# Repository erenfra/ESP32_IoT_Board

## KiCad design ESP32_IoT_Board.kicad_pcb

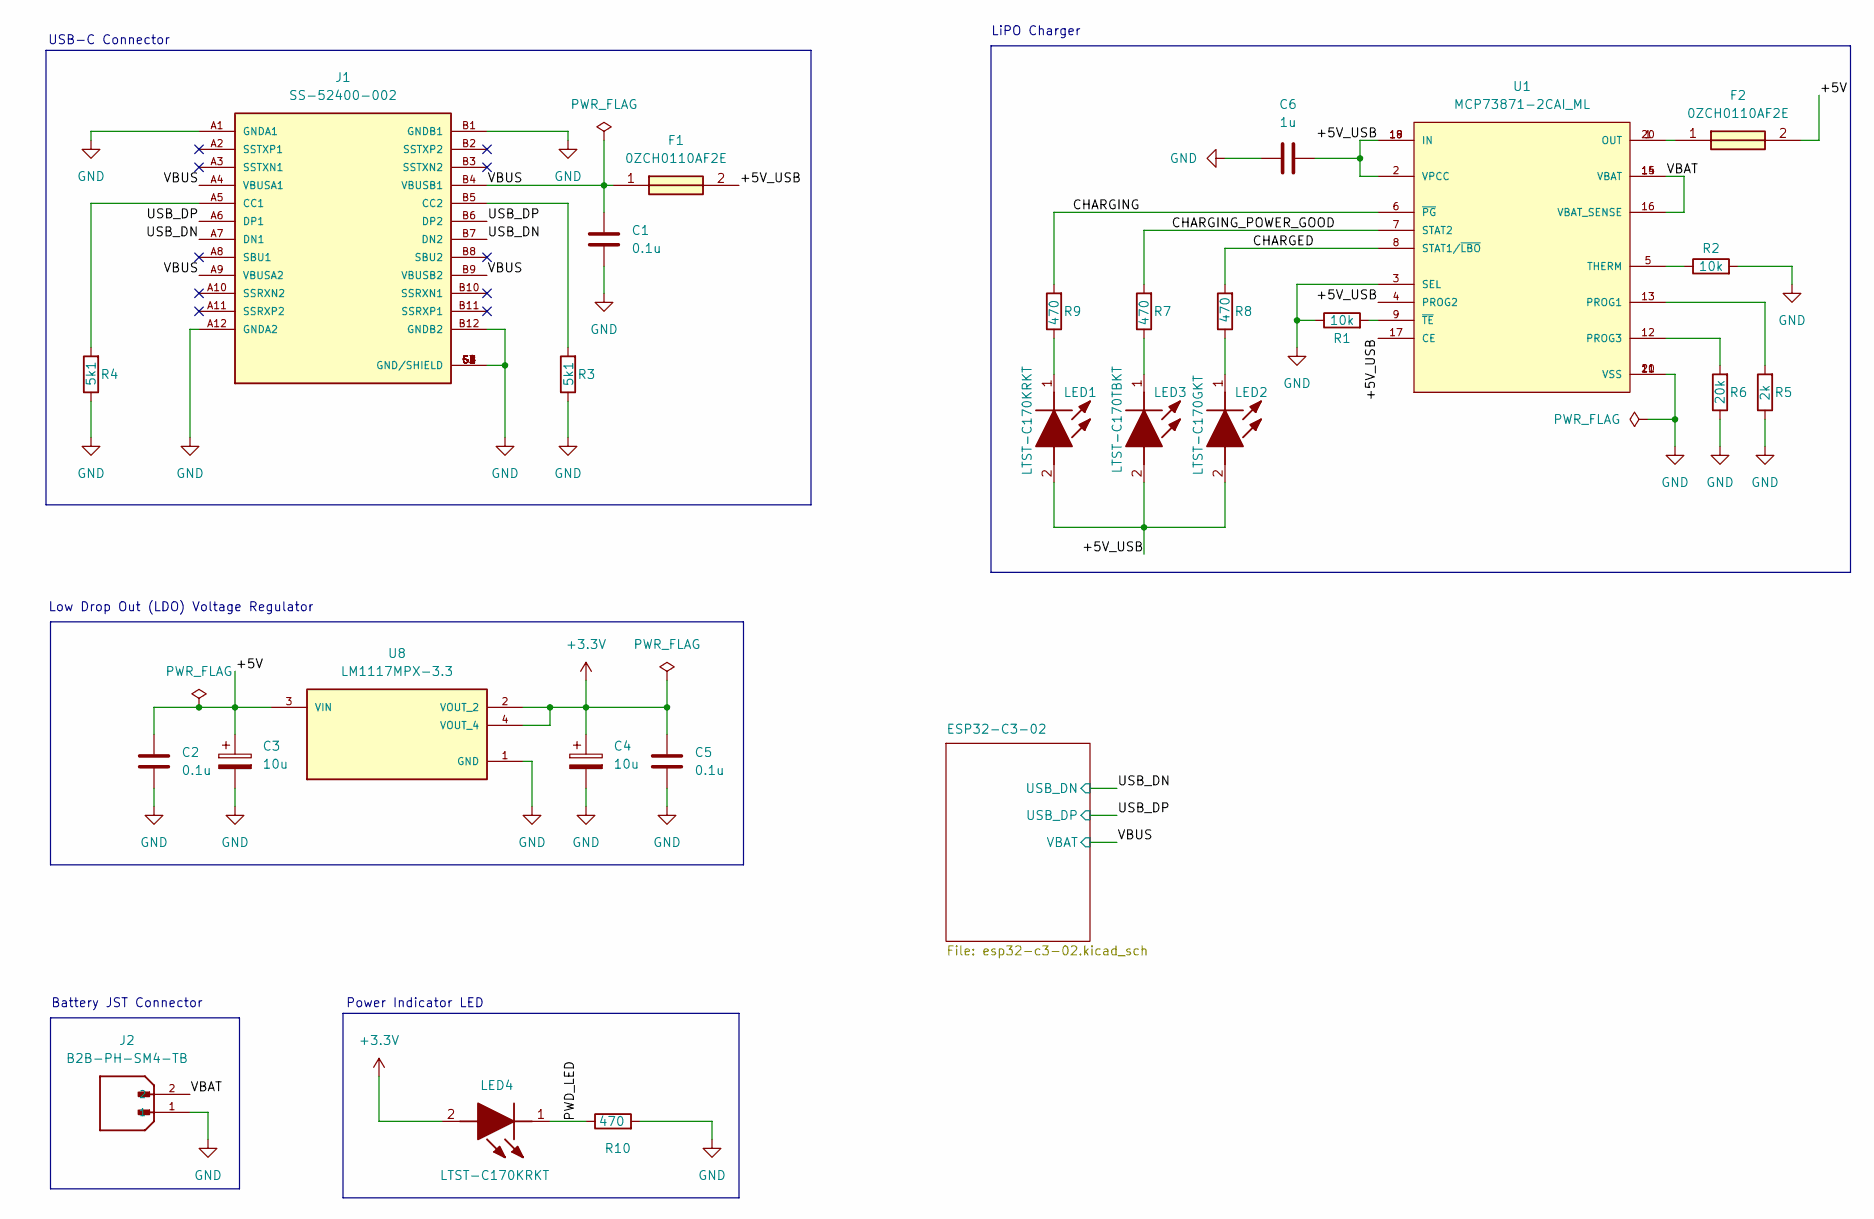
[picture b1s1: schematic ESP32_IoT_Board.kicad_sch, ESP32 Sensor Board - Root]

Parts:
C1, C2, C5: 0.1u; C_0805_2012Metric_Pad1.18x1.45mm_HandSolder
C3, C4: 10u; CP_EIA-3216-10_Kemet-I_HandSolder
C6: 1u; C_0805_2012Metric_Pad1.18x1.45mm_HandSolder
F1, F2: 0ZCH0110AF2E; FUSC3226X100N; Manufacturer_Part_Number 0ZCH0110AF2E
J1: SS-52400-002; BELFUSE_SS-52400-002; PARTREV A0
J2: B2B-PH-SM4-TB; JST_B2B-PH-SM4-TB; PARTREV N/A
LED1, LED4: LTST-C170KRKT; LEDC2012X120N; Manufacturer_Part_Number LTST-C170KRKT; Mouser Part Number 859-LTST-C170KRKT
LED2: LTST-C170GKT; LEDC2012X120N; Manufacturer_Part_Number LTST-C170GKT; Mouser Part Number 859-LTST-C170GKT
LED3: LTST-C170TBKT; LEDC2012X120N; Manufacturer_Part_Number LTST-C170TBKT; Mouser Part Number 859-LTST-C170TBKT
R1, R2: 10k; R_0805_2012Metric_Pad1.20x1.40mm_HandSolder
R3, R4: 5k1; R_0805_2012Metric_Pad1.20x1.40mm_HandSolder
R5: 2k; R_0805_2012Metric_Pad1.20x1.40mm_HandSolder
R6: 20k; R_0805_2012Metric_Pad1.20x1.40mm_HandSolder
R7, R8, R9, R10: 470; R_0805_2012Metric_Pad1.20x1.40mm_HandSolder
U1: MCP73871-2CAI_ML; QFN50P400X400X100-21N; PARTREV D
U8: LM1117MPX-3.3; VREG_LM1117MPX-3.3

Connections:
+3.3V: C4.1, C5.1, LED4.2 (A), U8.2 (VOUT_2), U8.4 (VOUT_4); also elsewhere on the board
/+5V: C2.1, C3.1, F2.2, U8.3 (VIN)
/+5V_USB: C6.1, F1.2, LED1.2 (A), LED2.2 (A), LED3.2 (A), U1.2 (VPCC), U1.4 (PROG2), U1.17 (CE), U1.18 (IN), U1.19 (IN)
/CHARGED: R8.2, U1.8 (STAT1/~LBO)
/CHARGING: R9.2, U1.6 (~PG)
/CHARGING_POWER_GOOD: R7.2, U1.7 (STAT2)
/PWD_LED: LED4.1 (K), R10.1
/USB_DN: J1.A7 (DN1), J1.B7 (DN2); also elsewhere on the board
/USB_DP: J1.A6 (DP1), J1.B6 (DP2); also elsewhere on the board
/VBAT: J2.2, U1.14 (VBAT), U1.15 (VBAT), U1.16 (VBAT_SENSE)
/VBUS: C1.1, F1.1, J1.A4 (VBUSA1), J1.A9 (VBUSA2), J1.B4 (VBUSB1), J1.B9 (VBUSB2); also elsewhere on the board
GND: C1.2, C2.2, C3.2, C4.2, C5.2, C6.2, J1.A1 (GNDA1), J1.A12 (GNDA2), J1.B1 (GNDB1), J1.B12 (GNDB2), J1.G1 (GND/SHIELD), J1.G2 (GND/SHIELD), J1.G3 (GND/SHIELD), J1.G4 (GND/SHIELD), J1.S1 (GND/SHIELD), J1.S2 (GND/SHIELD), J1.S3 (GND/SHIELD), J1.S4 (GND/SHIELD), J2.1, R1.1, R2.2, R3.1, R4.1, R5.1, R6.1, R10.2, U1.3 (SEL), U1.10 (VSS), U1.11 (VSS), U1.21 (VSS), U8.1 (GND); also elsewhere on the board
unnamed: F2.1, U1.1 (OUT), U1.20 (OUT)
unnamed: J1.A5 (CC1), R4.2
unnamed: J1.B5 (CC2), R3.2
unnamed: LED1.1 (K), R9.1
unnamed: LED2.1 (K), R8.1
unnamed: LED3.1 (K), R7.1
unnamed: R5.2, U1.13 (PROG1)
unnamed: R6.2, U1.12 (PROG3)
unnamed: R2.1, U1.5 (THERM)
unnamed: R1.2, U1.9 (~TE)

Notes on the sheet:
LiPO Charger
Power Indicator LED
USB-C Connector
Low Drop Out (LDO) Voltage Regulator
Battery JST Connector

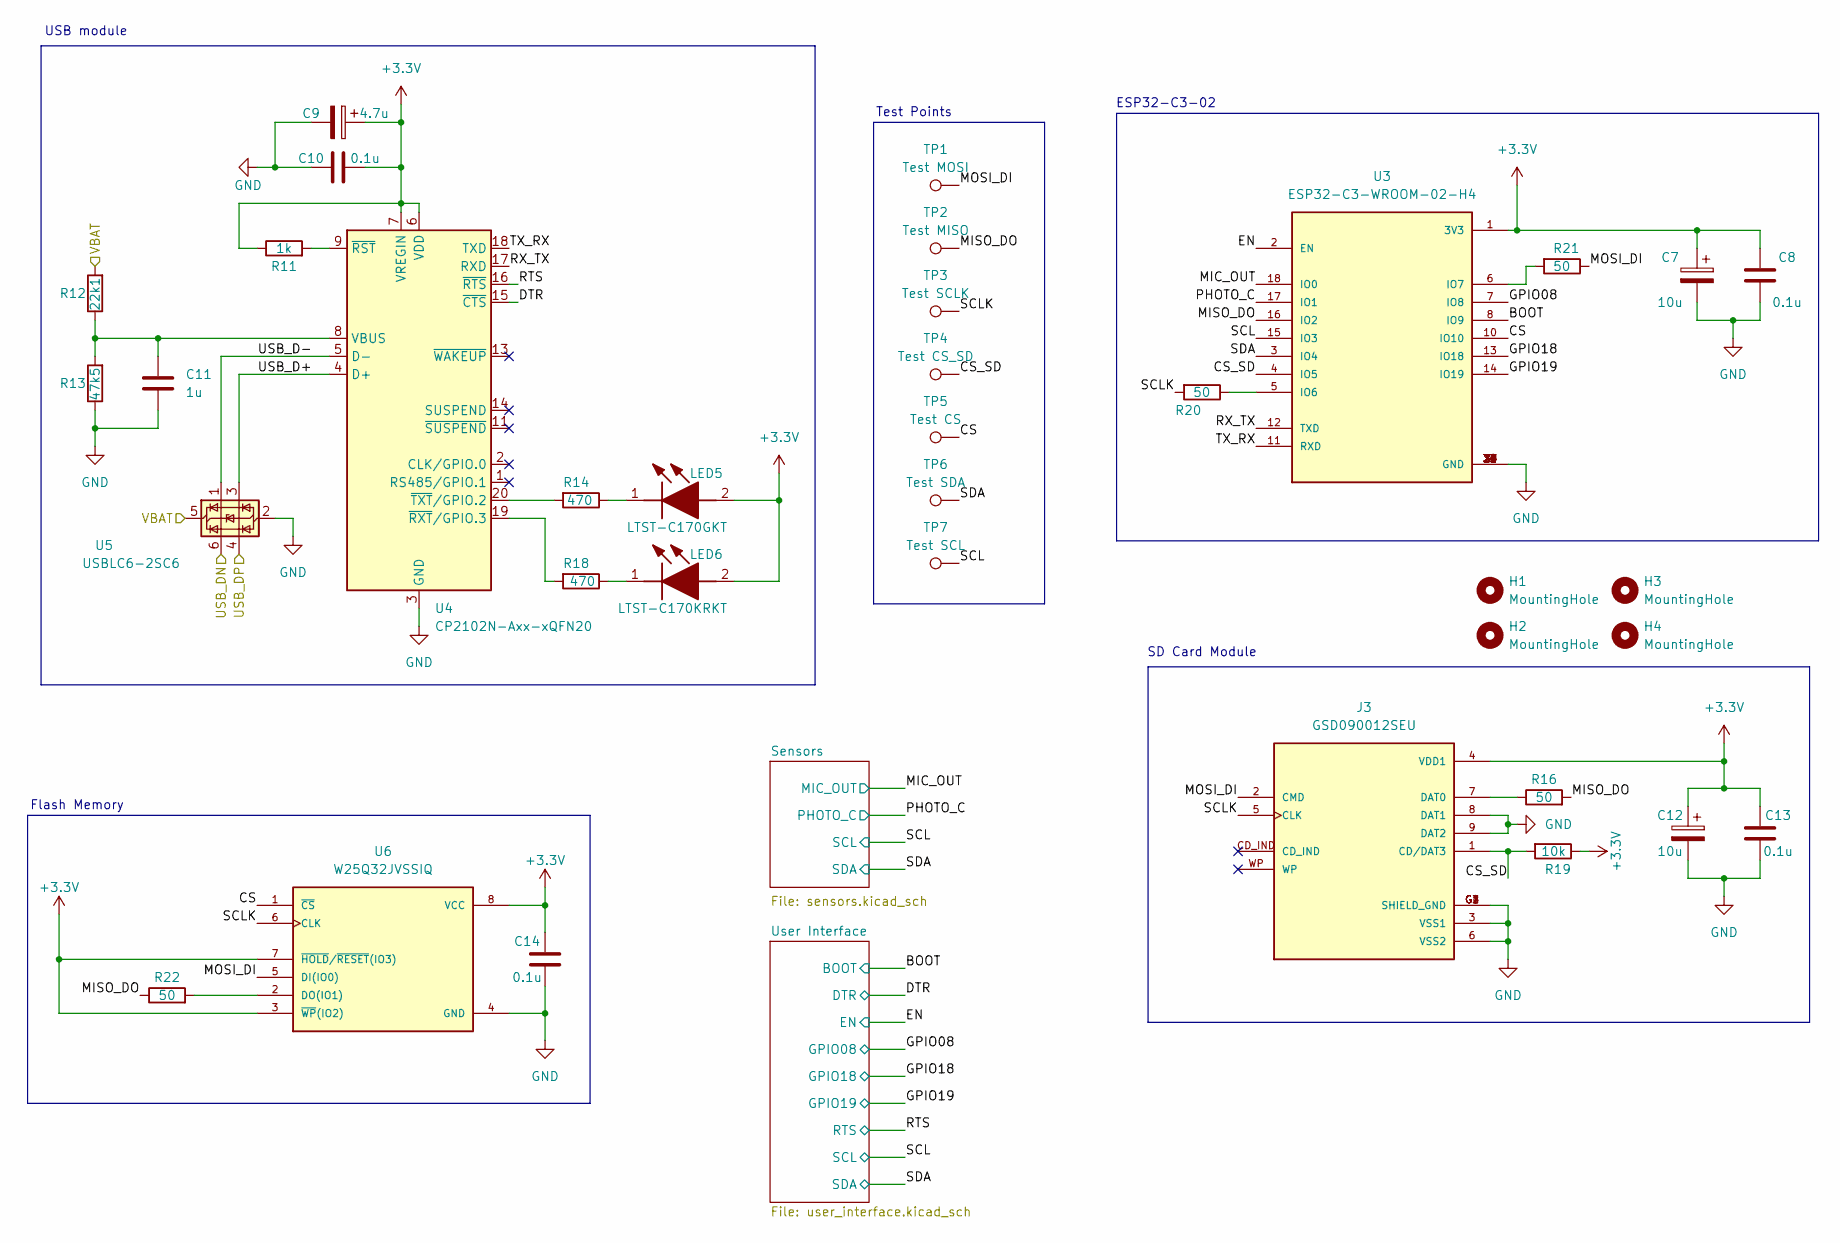
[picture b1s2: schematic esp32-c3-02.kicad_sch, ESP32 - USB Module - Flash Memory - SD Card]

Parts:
C7: 10u; CP_EIA-3216-10_Kemet-I_HandSolder
C8, C10, C13, C14: 0.1u; C_0805_2012Metric_Pad1.18x1.45mm_HandSolder
C9: 4.7u; CP_EIA-3216-10_Kemet-I_HandSolder
C11: 1u; C_0805_2012Metric_Pad1.18x1.45mm_HandSolder
C12: 10u; C_0805_2012Metric_Pad1.18x1.45mm_HandSolder
H1, H2, H3, H4: MountingHole; MountingHole_2.5mm
J3: GSD090012SEU; AMPHENOL_GSD090012SEU; PARTREV E
LED5: LTST-C170GKT; LEDC2012X120N; Manufacturer_Part_Number LTST-C170GKT; Mouser Part Number 859-LTST-C170GKT
LED6: LTST-C170KRKT; LEDC2012X120N; Manufacturer_Part_Number LTST-C170KRKT; Mouser Part Number 859-LTST-C170KRKT
R11: 1k; R_0805_2012Metric_Pad1.20x1.40mm_HandSolder
R12: 22k1; R_0805_2012Metric_Pad1.20x1.40mm_HandSolder
R13: 47k5; R_0805_2012Metric_Pad1.20x1.40mm_HandSolder
R14, R18: 470; R_0805_2012Metric_Pad1.20x1.40mm_HandSolder
R16, R20, R21, R22: 50; R_0805_2012Metric_Pad1.20x1.40mm_HandSolder
R19: 10k; R_0805_2012Metric_Pad1.20x1.40mm_HandSolder
TP1: Test MOSI; TestPoint_Pad_1.0x1.0mm
TP2: Test MISO; TestPoint_Pad_1.0x1.0mm
TP3: Test SCLK; TestPoint_Pad_1.0x1.0mm
TP4: Test CS_SD; TestPoint_Pad_1.0x1.0mm
TP5: Test CS; TestPoint_Pad_1.0x1.0mm
TP6: Test SDA; TestPoint_Pad_1.0x1.0mm
TP7: Test SCL; TestPoint_Pad_1.0x1.0mm
U3: ESP32-C3-WROOM-02-H4; MODULE_ESP32-C3-WROOM-02-H4
U4: CP2102N-Axx-xQFN20; SiliconLabs_QFN-20-1EP_3x3mm_P0.5mm_EP1.8x1.8mm
U5: USBLC6-2SC6; SOT-23-6
U6: W25Q32JVSSIQ; SOIC127P790X216-8N; M_PART_NUMBER W25QXX

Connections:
+3.3V: C7.1, C8.2, C9.1, C10.2, C12.1, C13.2, C14.2, J3.4 (VDD1), LED5.2 (A), LED6.2 (A), R11.1, R19.1, U3.1 (3V3), U4.6 (VDD), U4.7 (VREGIN), U6.3 (~WP(IO2)), U6.7 (~HOLD/~RESET(IO3)), U6.8 (VCC); also elsewhere on the board
/ESP32-C3-02/BOOT: U3.8 (IO9); also elsewhere on the board
/ESP32-C3-02/CS: TP5.1, U3.10 (IO10), U6.1 (~CS)
/ESP32-C3-02/CS_SD: J3.1 (CD/DAT3), R19.2, TP4.1, U3.4 (IO5)
/ESP32-C3-02/DTR: U4.15 (~CTS); also elsewhere on the board
/ESP32-C3-02/EN: U3.2 (EN); also elsewhere on the board
/ESP32-C3-02/GPIO08: U3.7 (IO8); also elsewhere on the board
/ESP32-C3-02/GPIO18: U3.13 (IO18); also elsewhere on the board
/ESP32-C3-02/GPIO19: U3.14 (IO19); also elsewhere on the board
/ESP32-C3-02/MIC_OUT: U3.18 (IO0); also elsewhere on the board
/ESP32-C3-02/MISO_DO: R16.2, R22.1, TP2.1, U3.16 (IO2)
/ESP32-C3-02/MOSI_DI: J3.2 (CMD), R21.1, TP1.1, U6.5 (DI(IO0))
/ESP32-C3-02/PHOTO_C: U3.17 (IO1); also elsewhere on the board
/ESP32-C3-02/RTS: U4.16 (~RTS); also elsewhere on the board
/ESP32-C3-02/RX_TX: U3.12 (TXD), U4.17 (RXD)
/ESP32-C3-02/SCL: TP7.1, U3.15 (IO3); also elsewhere on the board
/ESP32-C3-02/SCLK: J3.5 (CLK), R20.2, TP3.1, U6.6 (CLK)
/ESP32-C3-02/SDA: TP6.1, U3.3 (IO4); also elsewhere on the board
/ESP32-C3-02/TX_RX: U3.11 (RXD), U4.18 (TXD)
/ESP32-C3-02/USB_D+: U4.4 (D+), U5.3 (I/O2)
/ESP32-C3-02/USB_D-: U4.5 (D-), U5.1 (I/O1)
/USB_DN: U5.6 (I/O1); also elsewhere on the board
/USB_DP: U5.4 (I/O2); also elsewhere on the board
/VBUS: R12.2, U5.5 (VBUS); also elsewhere on the board
GND: C7.2, C8.1, C9.2, C10.1, C11.2, C12.2, C13.1, C14.1, J3.3 (VSS1), J3.6 (VSS2), J3.8 (DAT1), J3.9 (DAT2), J3.G1 (SHIELD_GND), J3.G2 (SHIELD_GND), J3.G3 (SHIELD_GND), J3.G4 (SHIELD_GND), R13.1, U3.9 (GND), U3.19 (GND), U3.20 (GND), U3.21 (GND), U3.22 (GND), U3.23 (GND), U3.24 (GND), U3.25 (GND), U3.26 (GND), U3.27 (GND), U3.28 (GND), U3.29 (GND), U3.30 (GND), U3.31 (GND), U3.32 (GND), U3.33 (GND), U3.34 (GND), U3.35 (GND), U3.36 (GND), U3.37 (GND), U3.38 (GND), U3.39 (GND), U4.3 (GND), U4.12 (GND), U4.21 (GND), U5.2 (GND), U6.4 (GND); also elsewhere on the board
unnamed: J3.7 (DAT0), R16.1
unnamed: LED5.1 (K), R14.1
unnamed: LED6.1 (K), R18.1
unnamed: R20.1, U3.5 (IO6)
unnamed: R21.2, U3.6 (IO7)
unnamed: C11.1, R12.1, R13.2, U4.8 (VBUS)
unnamed: R11.2, U4.9 (~RST)
unnamed: R18.2, U4.19 (~RXT/GPIO.3)
unnamed: R14.2, U4.20 (~TXT/GPIO.2)
unnamed: R22.2, U6.2 (DO(IO1))

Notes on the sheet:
Flash Memory
USB module
SD Card Module
Test Points
ESP32-C3-02

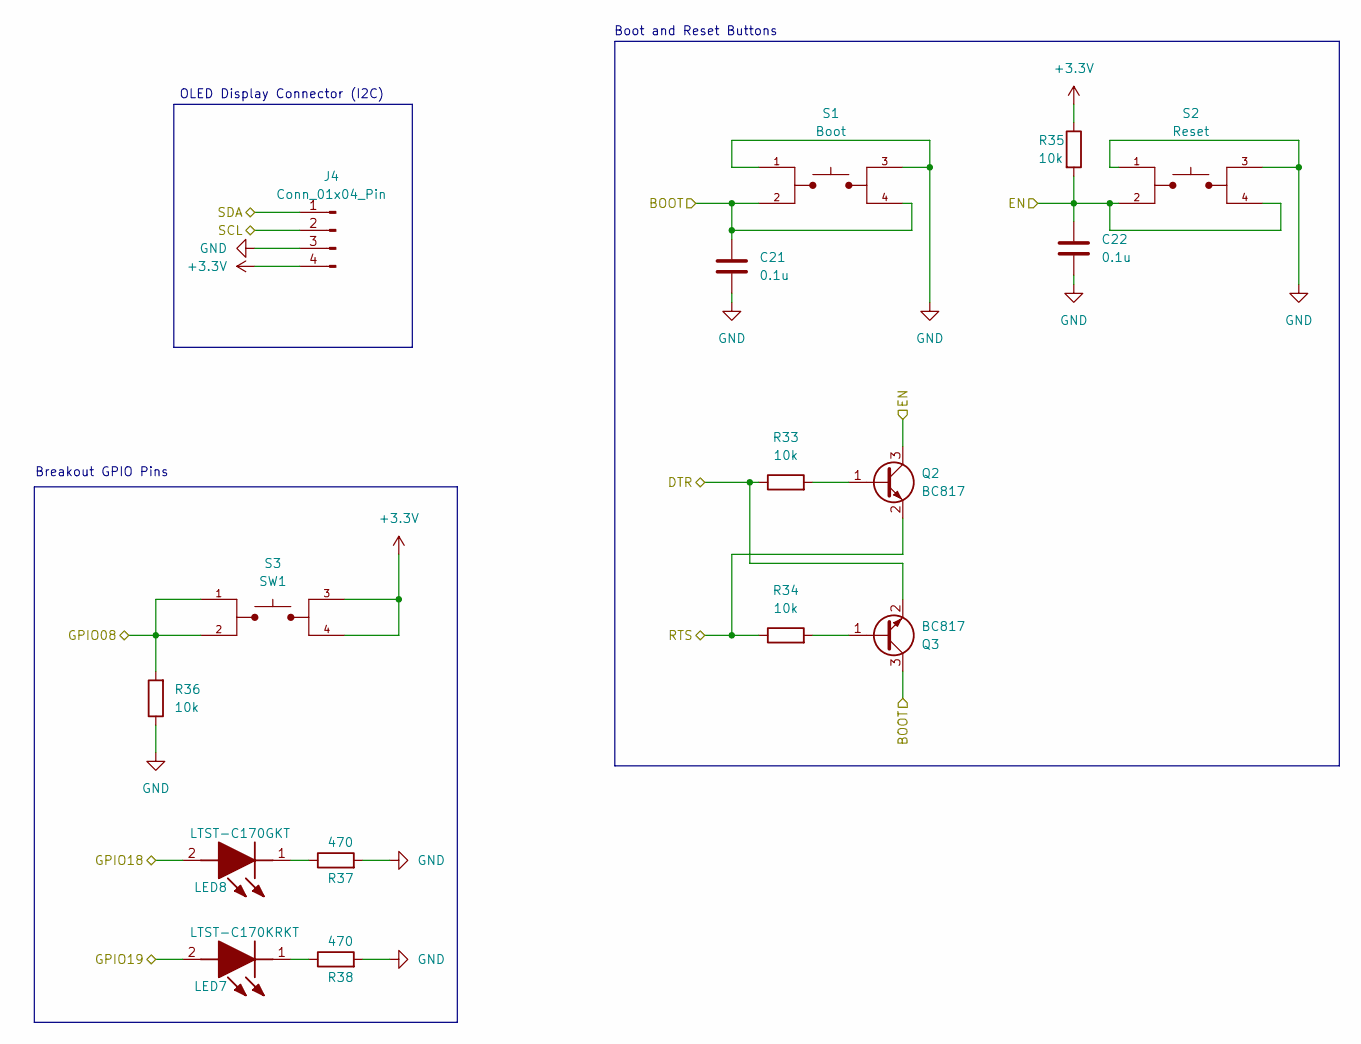
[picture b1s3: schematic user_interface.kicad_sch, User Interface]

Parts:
C21, C22: 0.1u; C_0805_2012Metric_Pad1.18x1.45mm_HandSolder
J4: Conn_01x04_Pin; PinHeader_1x04_P2.54mm_Vertical
LED7: LTST-C170KRKT; LEDC2012X120N; Manufacturer_Part_Number LTST-C170KRKT; Mouser Part Number 859-LTST-C170KRKT
LED8: LTST-C170GKT; LEDC2012X120N; Manufacturer_Part_Number LTST-C170GKT; Mouser Part Number 859-LTST-C170GKT
Q2, Q3: BC817; SOT-23
R33, R34, R35, R36: 10k; R_0805_2012Metric_Pad1.20x1.40mm_HandSolder
R37, R38: 470; R_0805_2012Metric_Pad1.20x1.40mm_HandSolder
S1: Boot; SW_TL3305AF260QG; PARTREV C
S2: Reset; SW_TL3305AF260QG; PARTREV C
S3: SW1; SW_TL3305AF260QG; PARTREV C

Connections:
+3.3V: J4.4, R35.1, S3.3, S3.4; also elsewhere on the board
/ESP32-C3-02/BOOT: C21.1, Q3.3 (C), S1.2, S1.4; also elsewhere on the board
/ESP32-C3-02/DTR: Q3.2 (E), R33.1; also elsewhere on the board
/ESP32-C3-02/EN: C22.1, Q2.3 (C), R35.2, S2.2, S2.4; also elsewhere on the board
/ESP32-C3-02/GPIO08: R36.2, S3.1, S3.2; also elsewhere on the board
/ESP32-C3-02/GPIO18: LED8.2 (A); also elsewhere on the board
/ESP32-C3-02/GPIO19: LED7.2 (A); also elsewhere on the board
/ESP32-C3-02/RTS: Q2.2 (E), R34.1; also elsewhere on the board
/ESP32-C3-02/SCL: J4.2; also elsewhere on the board
/ESP32-C3-02/SDA: J4.1; also elsewhere on the board
GND: C21.2, C22.2, J4.3, R36.1, R37.2, R38.2, S1.1, S1.3, S2.1, S2.3; also elsewhere on the board
unnamed: LED7.1 (K), R38.1
unnamed: LED8.1 (K), R37.1
unnamed: Q2.1 (B), R33.2
unnamed: Q3.1 (B), R34.2

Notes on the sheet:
Breakout GPIO Pins
Boot and Reset Buttons
OLED Display Connector (I2C)

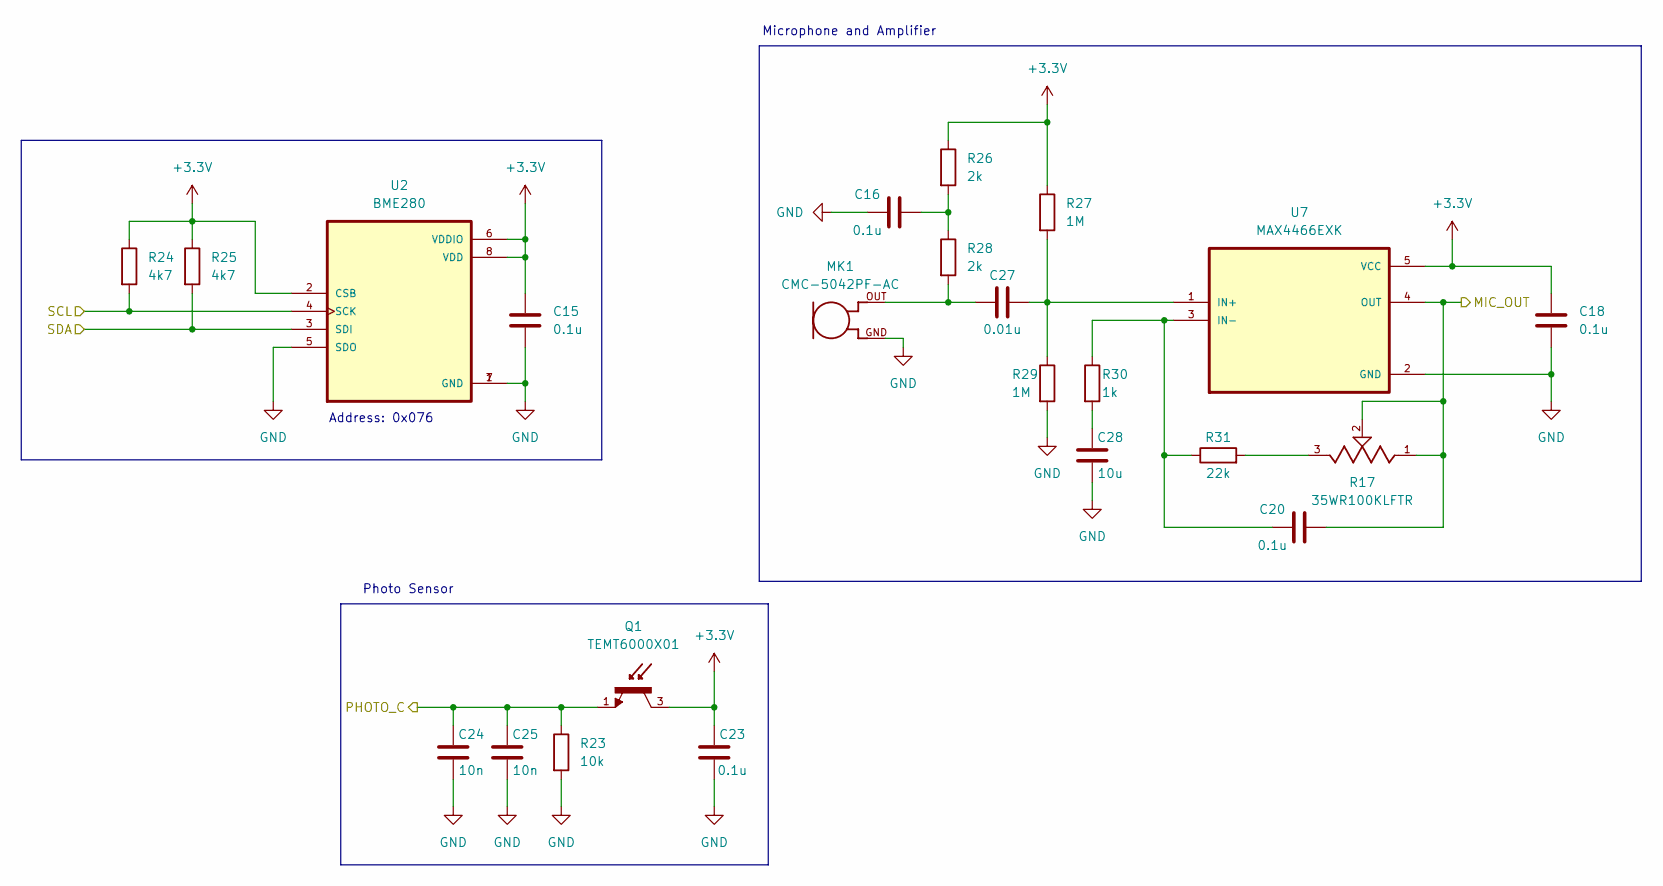
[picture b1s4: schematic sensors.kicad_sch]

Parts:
C15, C16, C18, C20, C23: 0.1u; C_0805_2012Metric_Pad1.18x1.45mm_HandSolder
C24, C25: 10n; C_0805_2012Metric_Pad1.18x1.45mm_HandSolder
C27: 0.01u; C_0805_2012Metric_Pad1.18x1.45mm_HandSolder
C28: 10u; C_0805_2012Metric_Pad1.18x1.45mm_HandSolder
MK1: CMC-5042PF-AC; CUI_CMC-5042PF-AC
Q1: TEMT6000X01; TRANS_TEMT6000X01; PARTREV 1.9
R17: 35WR100KLFTR; TRIM_35WR100KLFTR; PARTREV D
R23: 10k; R_0805_2012Metric_Pad1.20x1.40mm_HandSolder
R24, R25: 4k7; R_0805_2012Metric_Pad1.20x1.40mm_HandSolder
R26, R28: 2k; R_0805_2012Metric_Pad1.20x1.40mm_HandSolder
R27, R29: 1M; R_0805_2012Metric_Pad1.20x1.40mm_HandSolder
R30: 1k; R_0805_2012Metric_Pad1.20x1.40mm_HandSolder
R31: 22k; R_0805_2012Metric_Pad1.20x1.40mm_HandSolder
U2: BME280; PSON65P250X250X100-8N
U7: MAX4466EXK; SOT65P210X110-5N

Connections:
+3.3V: C15.1, C18.1, C23.1, Q1.3, R24.1, R25.1, R26.1, R27.1, U2.2 (CSB), U2.6 (VDDIO), U2.8 (VDD), U7.5 (VCC); also elsewhere on the board
/ESP32-C3-02/MIC_OUT: C20.1, R17.1, R17.2, U7.4 (OUT); also elsewhere on the board
/ESP32-C3-02/PHOTO_C: C24.1, C25.1, Q1.1, R23.1; also elsewhere on the board
/ESP32-C3-02/SCL: R24.2, U2.4 (SCK); also elsewhere on the board
/ESP32-C3-02/SDA: R25.2, U2.3 (SDI); also elsewhere on the board
GND: C15.2, C16.2, C18.2, C23.2, C24.2, C25.2, C28.2, MK1.GND, R23.2, R29.2, U2.1 (GND), U2.5 (SDO), U2.7 (GND), U7.2 (GND); also elsewhere on the board
unnamed: C16.1, R26.2, R28.1
unnamed: C27.2, MK1.OUT, R28.2
unnamed: C28.1, R30.2
unnamed: R17.3, R31.2
unnamed: C27.1, R27.2, R29.1, U7.1 (IN+)
unnamed: C20.2, R30.1, R31.1, U7.3 (IN-)

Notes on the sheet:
Photo Sensor
Microphone and Amplifier
Address: 0x076

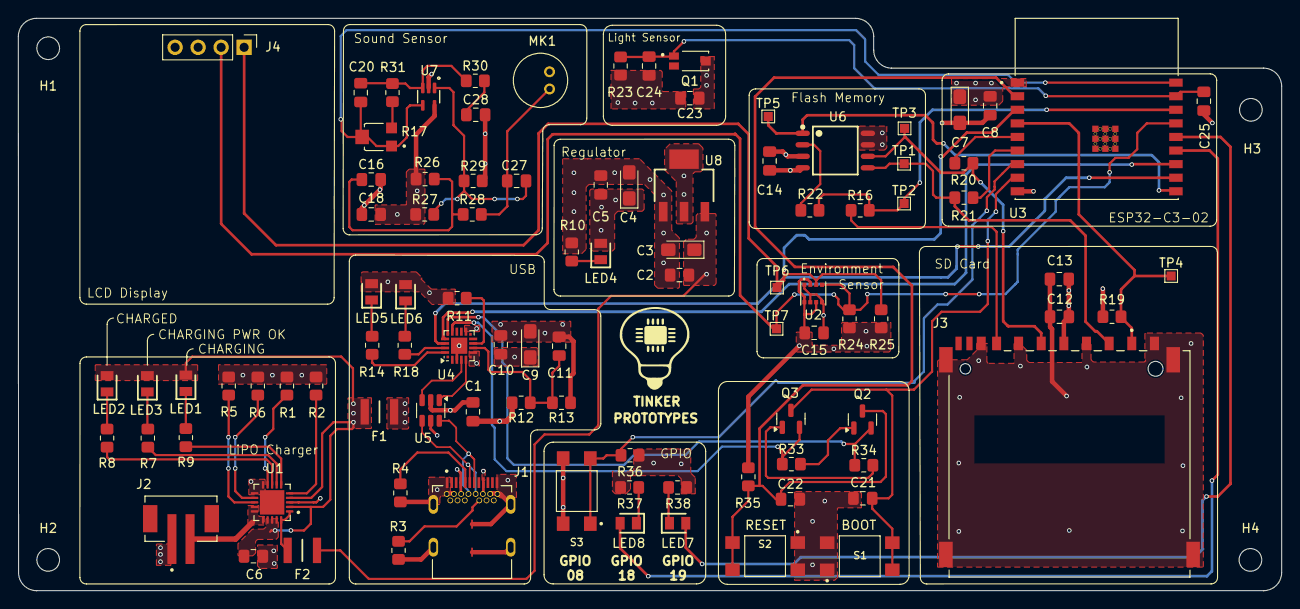
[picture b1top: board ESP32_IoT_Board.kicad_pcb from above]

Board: 4 copper layers, 139.5 x 63.2 mm, 101 parts (0 on the bottom side), 62 nets.

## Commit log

2025-05-20 First sheet completed
2025-05-23 SCH completed
2025-05-29 clean Warnings on the SCH
2025-06-09 PCB completed
2025-06-10 route completed
